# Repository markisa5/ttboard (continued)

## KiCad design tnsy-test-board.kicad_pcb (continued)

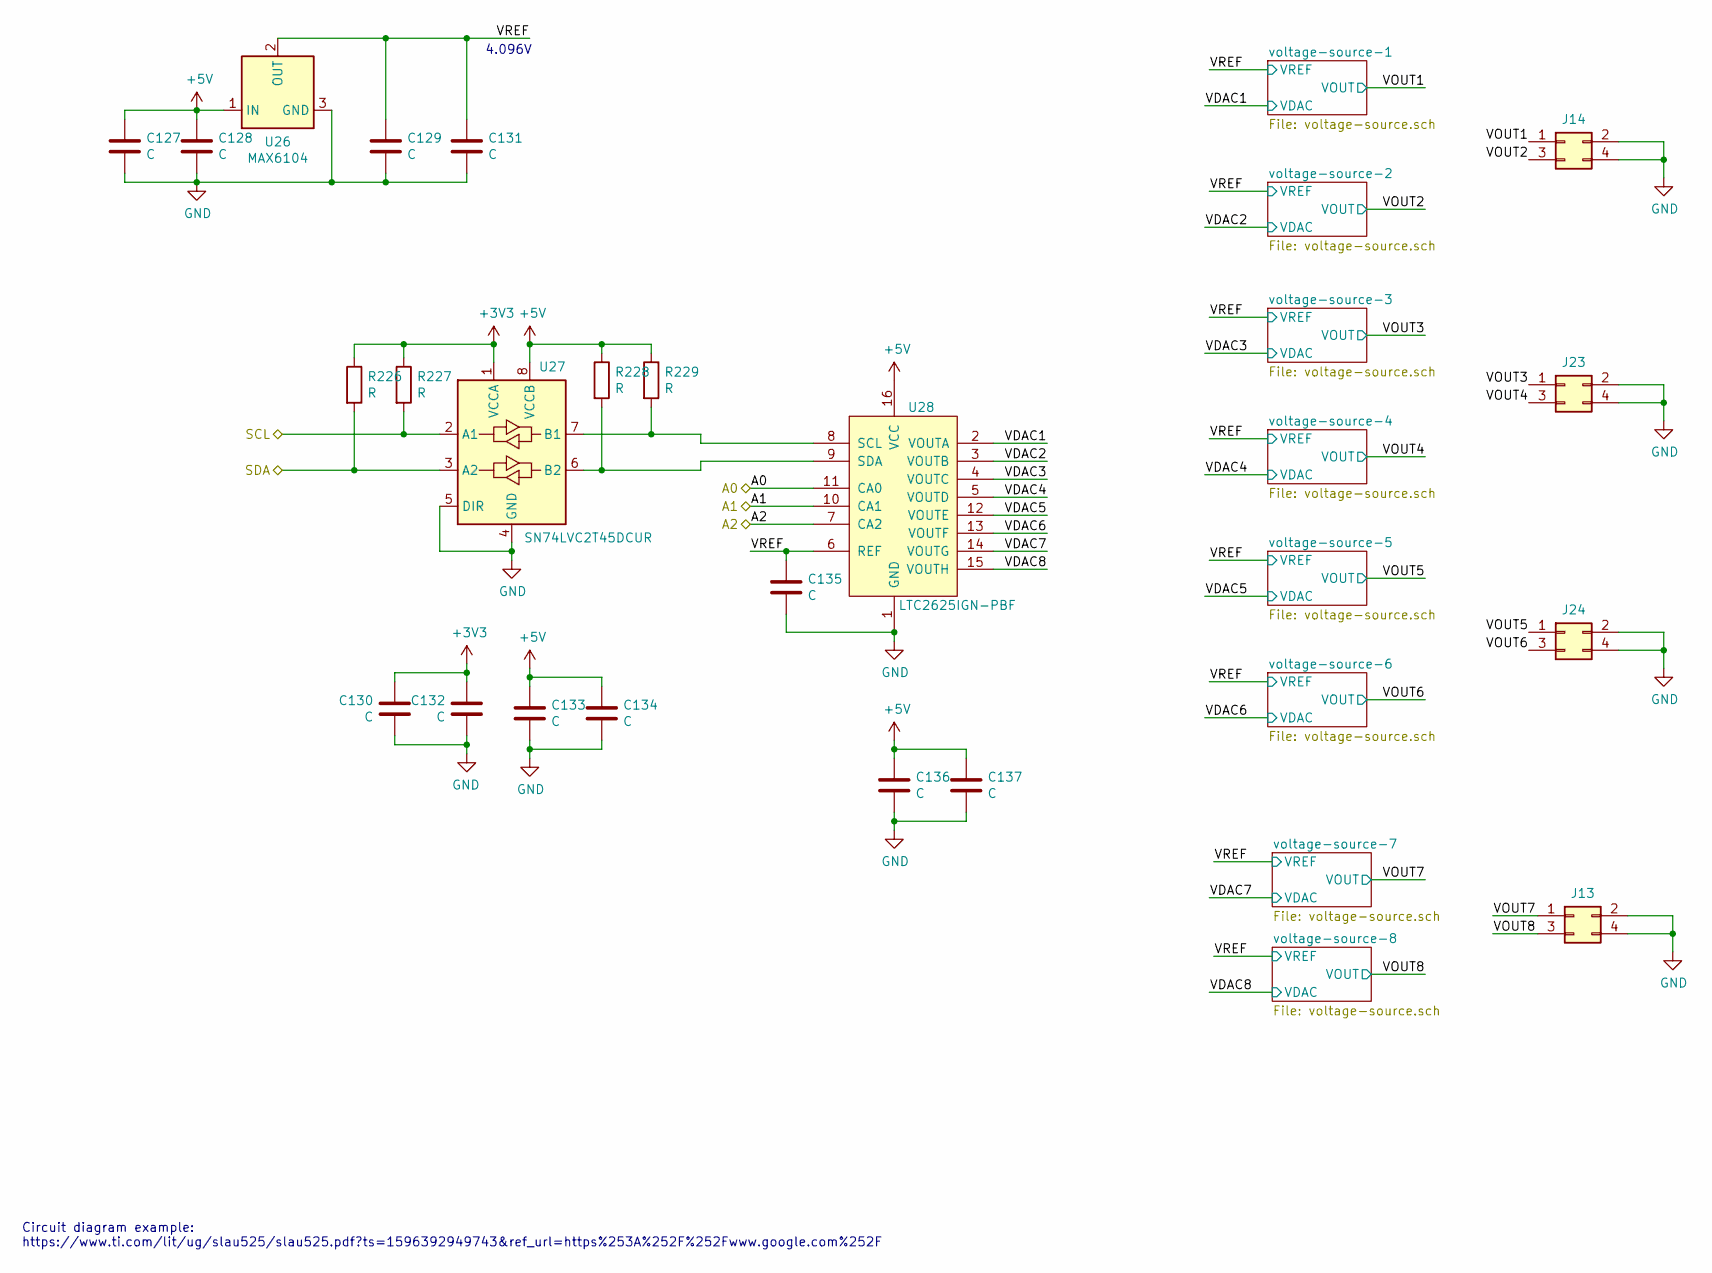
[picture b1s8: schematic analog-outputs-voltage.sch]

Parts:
C127, C128, C129, C130, C131, C132, C133, C134, C135, C136, C137: C; C_0603
J13, J14, J23, J24: Conn_02x02_Odd_Even; JST_EH_B04B-EH-A_04x2.50mm_Straight
R226, R227, R228, R229: R; R_0603
U26: MAX6104; SOT-23
U27: SN74LVC2T45DCUR; VSSOP-8_2.3x2mm_Pitch0.5mm
U28: LTC2625IGN-PBF; TSSOP-16_4.4x5mm_Pitch0.65mm

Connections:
+5V: C127.1, C128.1, C133.1, C134.1, C136.1, C137.1, R228.1, R229.1, U26.1 (IN), U27.8 (VCCB), U28.16 (VCC); also elsewhere on the board
/AO2_A0: U28.11 (CA0); also elsewhere on the board
/AO2_A1: U28.10 (CA1); also elsewhere on the board
/AO2_A2: U28.7 (CA2); also elsewhere on the board
/SCL2: R227.2, U27.2 (A1); also elsewhere on the board
/SDA2: R226.2, U27.3 (A2); also elsewhere on the board
/analog-outputs-2/VDAC1: U28.2 (VOUTA); also elsewhere on the board
/analog-outputs-2/VDAC2: U28.3 (VOUTB); also elsewhere on the board
/analog-outputs-2/VDAC3: U28.4 (VOUTC); also elsewhere on the board
/analog-outputs-2/VDAC4: U28.5 (VOUTD); also elsewhere on the board
/analog-outputs-2/VDAC5: U28.12 (VOUTE); also elsewhere on the board
/analog-outputs-2/VDAC6: U28.13 (VOUTF); also elsewhere on the board
/analog-outputs-2/VDAC7: U28.14 (VOUTG); also elsewhere on the board
/analog-outputs-2/VDAC8: U28.15 (VOUTH); also elsewhere on the board
/analog-outputs-2/VOUT1: J14.1; also elsewhere on the board
/analog-outputs-2/VOUT2: J14.3; also elsewhere on the board
/analog-outputs-2/VOUT3: J23.1; also elsewhere on the board
/analog-outputs-2/VOUT4: J23.3; also elsewhere on the board
/analog-outputs-2/VOUT5: J24.1; also elsewhere on the board
/analog-outputs-2/VOUT6: J24.3; also elsewhere on the board
/analog-outputs-2/VOUT7: J13.1; also elsewhere on the board
/analog-outputs-2/VOUT8: J13.3; also elsewhere on the board
/analog-outputs-2/VREF: C129.1, C131.1, C135.1, U26.2 (OUT), U28.6 (REF); also elsewhere on the board
GND: C127.2, C128.2, C129.2, C130.2, C131.2, C132.2, C133.2, C134.2, C135.2, C136.2, C137.2, J13.2, J13.4, J14.2, J14.4, J23.2, J23.4, J24.2, J24.4, U26.3 (GND), U27.4 (GND), U27.5 (DIR), U28.1 (GND); also elsewhere on the board
unnamed: R228.2, U27.6 (B2), U28.9 (SDA)
unnamed: R229.2, U27.7 (B1), U28.8 (SCL)

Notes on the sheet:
Circuit diagram example: https://www.ti.com/lit/ug/slau525/slau525.pdf?ts=1596392949743&ref_url=https%253A%252F%252Fwww.google.com%252F
4.096V

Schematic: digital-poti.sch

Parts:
C205: 10n; C_0603
C206, C207: 4.7u; C_0603
R287: 10k; R_0603
U39: MCP4451-103E_ST; TSSOP-20_4.4x6.5mm_Pitch0.65mm

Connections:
/DP1_A0: U39.4 (HVC/A0); also elsewhere on the board
/DP1_A1: U39.16 (A1); also elsewhere on the board
/SCL1: U39.5 (SCL); also elsewhere on the board
/SDA1: U39.6 (SDA); also elsewhere on the board
/T1A: U39.9 (P1W); also elsewhere on the board
/T1B: U39.8 (P1B); also elsewhere on the board
/T2A: U39.19 (P2W); also elsewhere on the board
/T2B: U39.18 (P2B); also elsewhere on the board
/T3A: U39.12 (P0W); also elsewhere on the board
/T3B: U39.13 (P0B); also elsewhere on the board
GND: C205.2, C206.2, C207.2, U39.7 (VSS); also elsewhere on the board
unnamed: R287.2, U39.15 (*RESET)

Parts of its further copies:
C202: 10n; C_0603
C203, C204: 4.7u; C_0603
R286: 10k; R_0603
U38: MCP4451-103E_ST; TSSOP-20_4.4x6.5mm_Pitch0.65mm

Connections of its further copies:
/DP2_A0: U38.4 (HVC/A0); also elsewhere on the board
/DP2_A1: U38.16 (A1); also elsewhere on the board
/SCL1: U38.5 (SCL); also elsewhere on the board
/SDA1: U38.6 (SDA); also elsewhere on the board
/T4A: U38.9 (P1W); also elsewhere on the board
/T4B: U38.8 (P1B); also elsewhere on the board
/T5A: U38.19 (P2W); also elsewhere on the board
/T5B: U38.18 (P2B); also elsewhere on the board
/T6A: U38.12 (P0W); also elsewhere on the board
/T6B: U38.13 (P0B); also elsewhere on the board
GND: C202.2, C203.2, C204.2, U38.7 (VSS); also elsewhere on the board
unnamed: R286.2, U38.15 (*RESET)

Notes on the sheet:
DIGITAL POTI

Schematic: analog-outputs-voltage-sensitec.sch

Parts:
C208, C209, C210, C211, C212, C213, C214, C215, C216, C217, C218: C; C_0603
J15, J16, J25, J26: Conn_02x02_Odd_Even; JST_EH_B04B-EH-A_04x2.50mm_Straight
R288, R289, R290, R291: R; R_0603
U40: MAX6104; SOT-23-3
U41: SN74LVC2T45DCUR; VSSOP-8_2.3x2mm_Pitch0.5mm
U42: LTC2625IGN-PBF; SSOP-16_3.9x4.9mm_Pitch0.635mm

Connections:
+5V: C208.1, C209.1, C214.1, C215.1, C217.1, C218.1, R290.1, R291.1, U40.1 (IN), U41.8 (VCCB), U42.16 (VCC); also elsewhere on the board
/AO3_A0: U42.11 (CA0); also elsewhere on the board
/AO3_A1: U42.10 (CA1); also elsewhere on the board
/AO3_A2: U42.7 (CA2); also elsewhere on the board
/SCL2: R289.2, U41.2 (A1); also elsewhere on the board
/SDA2: R288.2, U41.3 (A2); also elsewhere on the board
/analog-outputs-3/VDAC1: U42.2 (VOUTA); also elsewhere on the board
/analog-outputs-3/VDAC2: U42.3 (VOUTB); also elsewhere on the board
/analog-outputs-3/VDAC3: U42.4 (VOUTC); also elsewhere on the board
/analog-outputs-3/VDAC4: U42.5 (VOUTD); also elsewhere on the board
/analog-outputs-3/VDAC5: U42.12 (VOUTE); also elsewhere on the board
/analog-outputs-3/VDAC6: U42.13 (VOUTF); also elsewhere on the board
/analog-outputs-3/VDAC7: U42.14 (VOUTG); also elsewhere on the board
/analog-outputs-3/VDAC8: U42.15 (VOUTH); also elsewhere on the board
/analog-outputs-3/VOUT1: J16.1; also elsewhere on the board
/analog-outputs-3/VOUT2: J16.3; also elsewhere on the board
/analog-outputs-3/VOUT3: J25.1; also elsewhere on the board
/analog-outputs-3/VOUT4: J25.3; also elsewhere on the board
/analog-outputs-3/VOUT5: J26.1; also elsewhere on the board
/analog-outputs-3/VOUT6: J26.3; also elsewhere on the board
/analog-outputs-3/VOUT7: J15.1; also elsewhere on the board
/analog-outputs-3/VOUT8: J15.3; also elsewhere on the board
/analog-outputs-3/VREF: C210.1, C212.1, C216.1, U40.2 (OUT), U42.6 (REF); also elsewhere on the board
GND: C208.2, C209.2, C210.2, C211.2, C212.2, C213.2, C214.2, C215.2, C216.2, C217.2, C218.2, J15.2, J15.4, J16.2, J16.4, J25.2, J25.4, J26.2, J26.4, U40.3 (GND), U41.4 (GND), U41.5 (DIR), U42.1 (GND); also elsewhere on the board
unnamed: R290.2, U41.6 (B2), U42.9 (SDA)
unnamed: R291.2, U41.7 (B1), U42.8 (SCL)

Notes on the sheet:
Circuit diagram example: https://www.ti.com/lit/ug/slau525/slau525.pdf?ts=1596392949743&ref_url=https%253A%252F%252Fwww.google.com%252F
4.096V

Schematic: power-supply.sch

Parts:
C267, C268, C269, C270, C271, C272, C275, C276: C; C_0603
C273, C274: CP1; CP_Radial_D6.3mm_P2.50mm
C277, C278: 5600p; C_0603
C279, C280: 47p; C_0603
C281, C282: 100u; C_0603
C283, C285: 10u; C_0603
C284: 1u; C_0603
C286, C287: 100n; C_0603
D25: D; D_SMB
D26, D27: B560C-13-F; DO-214AB; MPN B560C-13-F; Digi-Key_PN B560C-FDICT-ND
F1: Fuse; Fuse_SMD1206_Wave
L1: L_Core_Ferrite_Coupled; CommonModeChoke_WuerthType-WE-CMB_Size-S
L2: 8.2u; Inductor_Wurth_HCI-1350
L3: 5.6u; Inductor_Wurth_HCI-1350
R324, R326: 330k; R_0603
R325, R327: 47k; R_0603
R328, R329: 162k; R_0603
R330, R331: 11.5k; R_0603
R332: 31.6k; R_0603
R333: 10.2k; R_0603
R334: 72.5k; R_0603
R335: 10k; R_0603
U51, U52: TPS54340DDA; PowerSOIC-8_W3.9mm

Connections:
+5V: C281.2, C283.2, C285.2, C287.2, L2.2, R334.1; also elsewhere on the board
+24V: F1.2; also elsewhere on the board
/power-supply/+24Vf: C267.1, C268.1, C269.1, C270.1, C271.1, C272.1, C273.1, C274.1, L1.2, R324.1, R326.1, U51.2 (VIN), U52.2 (VIN)
GND: C267.2, C268.2, C269.2, C270.2, C271.2, C272.2, C273.2, C274.2, C277.1, C278.1, C279.1, C280.1, C281.1, C282.1, C283.1, C284.1, C285.1, C286.1, C287.1, D26.A, D27.A, L1.4, R325.2, R327.2, R328.2, R329.2, R333.2, R335.2, U51.7 (GND), U51.9 (GNDPAD), U52.7 (GND), U52.9 (GNDPAD); also elsewhere on the board
GNDPWR: D25.2 (A), L1.3; also elsewhere on the board
unnamed: C275.1, U51.1 (BOOT)
unnamed: C275.2, D26.K, L2.1, U51.8 (SW)
unnamed: C276.1, U52.1 (BOOT)
unnamed: C276.2, D27.K, L3.1, U52.8 (SW)
unnamed: C277.2, R330.2
unnamed: C278.2, R331.2
unnamed: C279.2, R330.1, U51.6 (COMP)
unnamed: C280.2, R331.1, U52.6 (COMP)
unnamed: D25.1 (K), F1.1, L1.1
unnamed: R324.2, R325.1, U51.3 (EN)
unnamed: R326.2, R327.1, U52.3 (EN)
unnamed: R328.1, U51.4 (RT/CLK)
unnamed: R329.1, U52.4 (RT/CLK)
unnamed: R332.2, R333.1, U52.5 (FB)
unnamed: R334.2, R335.1, U51.5 (FB)

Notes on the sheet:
24V to 3.3V@3A
EN = pull down to disable < 1.2V
24V to 5V@3A
Add: 1. common mode filter (5Amps max design) 2. reverse polarity protection (5Amps max desing, 4Amps wcs) 3. overvoltage protection ( < 36V)

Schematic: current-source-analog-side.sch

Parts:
C18, C20, C22: 100n; C_0603
C19, C24: 4u7; C_0603
C21: 4.7u; C_0603
C23: C; C_0603
K1: EC2-3NU
Q1: SIR414DP-T1-GE3; TRANS_SQJ461EP-T1-GE3
Q2: BC817; SOT-23
Q3: Si2319BDS; SOT-23
R67, R68, R69, R70, R71: R; R_0603
R72, R73, R74: R; R_0805
U6, U7: OPA376xxD; SOIC-8_W3.9mm

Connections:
+5V: C18.1, C19.1, C20.1, C21.1, C22.1, C24.1, Q2.3 (C), U6.7 (V+), U7.7 (V+); also elsewhere on the board
/DIR1: Q2.1 (B), R69.1; also elsewhere on the board
/analog-outputs-1/A01+: K1.9; also elsewhere on the board
/analog-outputs-1/A01-: K1.4; also elsewhere on the board
/analog-outputs-1/VDAC1: U6.3 (+); also elsewhere on the board
/analog-outputs-1/current-source-1/VPOS: K1.3, K1.8, Q3.2 (S)
GND: C18.2, C19.2, C20.2, C21.2, C22.2, C24.2, K1.5, K1.10, R68.2, R69.2, R71.2, U6.4 (V-), U7.4 (V-); also elsewhere on the board
unnamed: C23.1, Q3.1 (G), R70.1, U7.6
unnamed: C23.2, R70.2, U7.2 (-)
unnamed: K1.1, Q2.2 (E)
unnamed: K1.12, R71.1
unnamed: Q1.1, Q1.2, Q1.3, R68.1, U6.2 (-)
unnamed: Q1.4, U6.6
unnamed: Q1.5, Q1.6, Q1.7, Q1.8, Q1.9, R67.2, U7.3 (+)
unnamed: Q3.3 (D), R72.2, R73.2, R74.2

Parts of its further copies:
C25, C27, C29, C32, C34, C36, C39, C41, C43, C46, C48, C50, C53, C55, C57, C60, C62, C64, C67, C69, C71: 100n; C_0603
C26, C31, C33, C38, C40, C45, C47, C52, C54, C59, C61, C66, C68, C73: 4u7; C_0603
C28, C35, C42, C49, C56, C63, C70: 4.7u; C_0603
C30, C37, C44, C51, C58, C65, C72: C; C_0603
K2, K3, K4, K5, K6, K7, K8: EC2-3NU
Q4, Q7, Q10, Q13, Q16, Q19, Q22: SIR414DP-T1-GE3; TRANS_SQJ461EP-T1-GE3
Q5, Q8, Q11, Q14, Q17, Q20, Q23: BC817; SOT-23
Q6, Q9, Q12, Q15, Q18, Q21, Q24: Si2319BDS; SOT-23
R75, R76, R77, R78, R79, R83, R84, R85, R86, R87, R91, R92, R93, R94, R95, R99, R100, R101, R102, R103, R107, R108, R109, R110, R111, R115, R116, R117, R118, R119, R123, R124, R125, R126, R127: R; R_0603
R80, R81, R82, R88, R89, R90, R96, R97, R98, R104, R105, R106, R112, R113, R114, R120, R121, R122, R128, R129, R130: R; R_0805
U8, U9, U10, U11, U12, U13, U14, U15, U16, U17, U18, U19, U20, U21: OPA376xxD; SOIC-8_W3.9mm

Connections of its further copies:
+5V: C25.1, C26.1, C27.1, C28.1, C29.1, C31.1, C32.1, C33.1, C34.1, C35.1, C36.1, C38.1, C39.1, C40.1, C41.1, C42.1, C43.1, C45.1, C46.1, C47.1, C48.1, C49.1, C50.1, C52.1, C53.1, C54.1, C55.1, C56.1, C57.1, C59.1, C60.1, C61.1, C62.1, C63.1, C64.1, C66.1, C67.1, C68.1, C69.1, C70.1, C71.1, C73.1, Q5.3 (C), Q8.3 (C), Q11.3 (C), Q14.3 (C), Q17.3 (C), Q20.3 (C), Q23.3 (C), U8.7 (V+), U9.7 (V+), U10.7 (V+), U11.7 (V+), U12.7 (V+), U13.7 (V+), U14.7 (V+), U15.7 (V+), U16.7 (V+), U17.7 (V+), U18.7 (V+), U19.7 (V+), U20.7 (V+), U21.7 (V+); also elsewhere on the board
/DIR2: Q5.1 (B), R77.1; also elsewhere on the board
/DIR3: Q8.1 (B), R85.1; also elsewhere on the board
/DIR4: Q11.1 (B), R93.1; also elsewhere on the board
/DIR5: Q14.1 (B), R101.1; also elsewhere on the board
/DIR6: Q17.1 (B), R109.1; also elsewhere on the board
/DIR7: Q20.1 (B), R117.1; also elsewhere on the board
/analog-outputs-1/A02+: K2.9; also elsewhere on the board
/analog-outputs-1/A02-: K2.4; also elsewhere on the board
/analog-outputs-1/A03+: K3.9; also elsewhere on the board
/analog-outputs-1/A03-: K3.4; also elsewhere on the board
/analog-outputs-1/A04+: K4.9; also elsewhere on the board
/analog-outputs-1/A04-: K4.4; also elsewhere on the board
/analog-outputs-1/A05+: K5.9; also elsewhere on the board
/analog-outputs-1/A05-: K5.4; also elsewhere on the board
/analog-outputs-1/A06+: K6.9; also elsewhere on the board
/analog-outputs-1/A06-: K6.4; also elsewhere on the board
/analog-outputs-1/A07+: K7.9; also elsewhere on the board
/analog-outputs-1/A07-: K7.4; also elsewhere on the board
/analog-outputs-1/A08+: K8.9; also elsewhere on the board
/analog-outputs-1/A08-: K8.4; also elsewhere on the board
/analog-outputs-1/POL8: Q23.1 (B), R125.1
/analog-outputs-1/VDAC2: U8.3 (+); also elsewhere on the board
/analog-outputs-1/VDAC3: U10.3 (+); also elsewhere on the board
/analog-outputs-1/VDAC4: U12.3 (+); also elsewhere on the board
/analog-outputs-1/VDAC5: U14.3 (+); also elsewhere on the board
/analog-outputs-1/VDAC6: U16.3 (+); also elsewhere on the board
/analog-outputs-1/VDAC7: U18.3 (+); also elsewhere on the board
/analog-outputs-1/VDAC8: U20.3 (+); also elsewhere on the board
/analog-outputs-1/current-source-2/VPOS: K2.3, K2.8, Q6.2 (S)
/analog-outputs-1/current-source-3/VPOS: K3.3, K3.8, Q9.2 (S)
/analog-outputs-1/current-source-4/VPOS: K4.3, K4.8, Q12.2 (S)
/analog-outputs-1/current-source-5/VPOS: K5.3, K5.8, Q15.2 (S)
/analog-outputs-1/current-source-6/VPOS: K6.3, K6.8, Q18.2 (S)
/analog-outputs-1/current-source-spare-1/VPOS: K7.3, K7.8, Q21.2 (S)
/analog-outputs-1/current-source-spare-2/VPOS: K8.3, K8.8, Q24.2 (S)
GND: C25.2, C26.2, C27.2, C28.2, C29.2, C31.2, C32.2, C33.2, C34.2, C35.2, C36.2, C38.2, C39.2, C40.2, C41.2, C42.2, C43.2, C45.2, C46.2, C47.2, C48.2, C49.2, C50.2, C52.2, C53.2, C54.2, C55.2, C56.2, C57.2, C59.2, C60.2, C61.2, C62.2, C63.2, C64.2, C66.2, C67.2, C68.2, C69.2, C70.2, C71.2, C73.2, K2.5, K2.10, K3.5, K3.10, K4.5, K4.10, K5.5, K5.10, K6.5, K6.10, K7.5, K7.10, K8.5, K8.10, R76.2, R77.2, R79.2, R84.2, R85.2, R87.2, R92.2, R93.2, R95.2, R100.2, R101.2, R103.2, R108.2, R109.2, R111.2, R116.2, R117.2, R119.2, R124.2, R125.2, R127.2, U8.4 (V-), U9.4 (V-), U10.4 (V-), U11.4 (V-), U12.4 (V-), U13.4 (V-), U14.4 (V-), U15.4 (V-), U16.4 (V-), U17.4 (V-), U18.4 (V-), U19.4 (V-), U20.4 (V-), U21.4 (V-); also elsewhere on the board
unnamed: C30.1, Q6.1 (G), R78.1, U9.6
unnamed: C30.2, R78.2, U9.2 (-)
unnamed: C37.1, Q9.1 (G), R86.1, U11.6
unnamed: C37.2, R86.2, U11.2 (-)
unnamed: C44.1, Q12.1 (G), R94.1, U13.6
unnamed: C44.2, R94.2, U13.2 (-)
unnamed: C51.1, Q15.1 (G), R102.1, U15.6
unnamed: C51.2, R102.2, U15.2 (-)
unnamed: C58.1, Q18.1 (G), R110.1, U17.6
unnamed: C58.2, R110.2, U17.2 (-)
unnamed: C65.1, Q21.1 (G), R118.1, U19.6
unnamed: C65.2, R118.2, U19.2 (-)
unnamed: C72.1, Q24.1 (G), R126.1, U21.6
unnamed: C72.2, R126.2, U21.2 (-)
unnamed: K2.1, Q5.2 (E)
unnamed: K2.12, R79.1
unnamed: K3.1, Q8.2 (E)
unnamed: K3.12, R87.1
unnamed: K4.1, Q11.2 (E)
unnamed: K4.12, R95.1
unnamed: K5.1, Q14.2 (E)
unnamed: K5.12, R103.1
unnamed: K6.1, Q17.2 (E)
unnamed: K6.12, R111.1
unnamed: K7.1, Q20.2 (E)
unnamed: K7.12, R119.1
unnamed: K8.1, Q23.2 (E)
unnamed: K8.12, R127.1
unnamed: Q4.1, Q4.2, Q4.3, R76.1, U8.2 (-)
unnamed: Q4.4, U8.6
unnamed: Q4.5, Q4.6, Q4.7, Q4.8, Q4.9, R75.2, U9.3 (+)
unnamed: Q6.3 (D), R80.2, R81.2, R82.2
unnamed: Q7.1, Q7.2, Q7.3, R84.1, U10.2 (-)
unnamed: Q7.4, U10.6
unnamed: Q7.5, Q7.6, Q7.7, Q7.8, Q7.9, R83.2, U11.3 (+)
unnamed: Q9.3 (D), R88.2, R89.2, R90.2
unnamed: Q10.1, Q10.2, Q10.3, R92.1, U12.2 (-)
unnamed: Q10.4, U12.6
unnamed: Q10.5, Q10.6, Q10.7, Q10.8, Q10.9, R91.2, U13.3 (+)
unnamed: Q12.3 (D), R96.2, R97.2, R98.2
unnamed: Q13.1, Q13.2, Q13.3, R100.1, U14.2 (-)
unnamed: Q13.4, U14.6
unnamed: Q13.5, Q13.6, Q13.7, Q13.8, Q13.9, R99.2, U15.3 (+)
unnamed: Q15.3 (D), R104.2, R105.2, R106.2
unnamed: Q16.1, Q16.2, Q16.3, R108.1, U16.2 (-)
unnamed: Q16.4, U16.6
unnamed: Q16.5, Q16.6, Q16.7, Q16.8, Q16.9, R107.2, U17.3 (+)
unnamed: Q18.3 (D), R112.2, R113.2, R114.2
unnamed: Q19.1, Q19.2, Q19.3, R116.1, U18.2 (-)
unnamed: Q19.4, U18.6
unnamed: Q19.5, Q19.6, Q19.7, Q19.8, Q19.9, R115.2, U19.3 (+)
unnamed: Q21.3 (D), R120.2, R121.2, R122.2
unnamed: Q22.1, Q22.2, Q22.3, R124.1, U20.2 (-)
unnamed: Q22.4, U20.6
unnamed: Q22.5, Q22.6, Q22.7, Q22.8, Q22.9, R123.2, U21.3 (+)
unnamed: Q24.3 (D), R128.2, R129.2, R130.2

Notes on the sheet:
RLOAD
3.3V

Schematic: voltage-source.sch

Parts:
C138, C139, C140, C141, C142, C143: C; C_0603
R230, R231, R232, R233: R; R_0603
U29: OPA188xxD; SOIC-8_W3.9mm

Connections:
+5V: C140.2, C142.2, U29.7 (V+); also elsewhere on the board
/analog-outputs-2/VDAC1: U29.3 (+); also elsewhere on the board
/analog-outputs-2/VOUT1: C143.2, R232.1, R233.1; also elsewhere on the board
/analog-outputs-2/VREF: R230.2; also elsewhere on the board
GND: C138.1, C140.1, C141.1, C142.1, C143.1, R231.1; also elsewhere on the board
unnamed: C138.2, C141.2, U29.4 (V-)
unnamed: C139.1, R233.2, U29.6
unnamed: C139.2, R230.1, R231.2, R232.2, U29.2 (-)

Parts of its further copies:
C144, C145, C146, C147, C148, C149, C150, C151, C152, C153, C154, C155, C156, C157, C158, C159, C160, C161, C162, C163, C164, C165, C166, C167, C168, C169, C170, C171, C172, C173, C174, C175, C176, C177, C178, C179, C180, C181, C182, C183, C184, C185, C219, C220, C221, C222, C223, C224, C225, C226, C227, C228, C229, C230, C231, C232, C233, C234, C235, C236, C237, C238, C239, C240, C241, C242, C243, C244, C245, C246, C247, C248, C249, C250, C251, C252, C253, C254, C255, C256, C257, C258, C259, C260, C261, C262, C263, C264, C265, C266: C; C_0603
R234, R235, R236, R237, R238, R239, R240, R241, R242, R243, R244, R245, R246, R247, R248, R249, R250, R251, R252, R253, R254, R255, R256, R257, R258, R259, R260, R261, R292, R293, R294, R295, R296, R297, R298, R299, R300, R301, R302, R303, R304, R305, R306, R307, R308, R309, R310, R311, R312, R313, R314, R315, R316, R317, R318, R319, R320, R321, R322, R323: R; R_0603
U30, U31, U32, U33, U34, U35, U36, U43, U44, U45, U46, U47, U48, U49, U50: OPA188xxD; SOIC-8_W3.9mm

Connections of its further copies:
+5V: C146.2, C148.2, C152.2, C154.2, C158.2, C160.2, C164.2, C166.2, C170.2, C172.2, C176.2, C178.2, C182.2, C184.2, C221.2, C223.2, C227.2, C229.2, C233.2, C235.2, C239.2, C241.2, C245.2, C247.2, C251.2, C253.2, C257.2, C259.2, C263.2, C265.2, U30.7 (V+), U31.7 (V+), U32.7 (V+), U33.7 (V+), U34.7 (V+), U35.7 (V+), U36.7 (V+), U43.7 (V+), U44.7 (V+), U45.7 (V+), U46.7 (V+), U47.7 (V+), U48.7 (V+), U49.7 (V+), U50.7 (V+); also elsewhere on the board
/analog-outputs-2/VDAC2: U30.3 (+); also elsewhere on the board
/analog-outputs-2/VDAC3: U31.3 (+); also elsewhere on the board
/analog-outputs-2/VDAC4: U32.3 (+); also elsewhere on the board
/analog-outputs-2/VDAC5: U33.3 (+); also elsewhere on the board
/analog-outputs-2/VDAC6: U34.3 (+); also elsewhere on the board
/analog-outputs-2/VDAC7: U35.3 (+); also elsewhere on the board
/analog-outputs-2/VDAC8: U36.3 (+); also elsewhere on the board
/analog-outputs-2/VOUT2: C149.2, R236.1, R237.1; also elsewhere on the board
/analog-outputs-2/VOUT3: C155.2, R240.1, R241.1; also elsewhere on the board
/analog-outputs-2/VOUT4: C161.2, R244.1, R245.1; also elsewhere on the board
/analog-outputs-2/VOUT5: C167.2, R248.1, R249.1; also elsewhere on the board
/analog-outputs-2/VOUT6: C173.2, R252.1, R253.1; also elsewhere on the board
/analog-outputs-2/VOUT7: C179.2, R256.1, R257.1; also elsewhere on the board
/analog-outputs-2/VOUT8: C185.2, R260.1, R261.1; also elsewhere on the board
/analog-outputs-2/VREF: R234.2, R238.2, R242.2, R246.2, R250.2, R254.2, R258.2; also elsewhere on the board
/analog-outputs-3/VDAC1: U43.3 (+); also elsewhere on the board
/analog-outputs-3/VDAC2: U44.3 (+); also elsewhere on the board
/analog-outputs-3/VDAC3: U45.3 (+); also elsewhere on the board
/analog-outputs-3/VDAC4: U46.3 (+); also elsewhere on the board
/analog-outputs-3/VDAC5: U47.3 (+); also elsewhere on the board
/analog-outputs-3/VDAC6: U48.3 (+); also elsewhere on the board
/analog-outputs-3/VDAC7: U49.3 (+); also elsewhere on the board
/analog-outputs-3/VDAC8: U50.3 (+); also elsewhere on the board
/analog-outputs-3/VOUT1: C224.2, R294.1, R295.1; also elsewhere on the board
/analog-outputs-3/VOUT2: C230.2, R298.1, R299.1; also elsewhere on the board
/analog-outputs-3/VOUT3: C236.2, R302.1, R303.1; also elsewhere on the board
/analog-outputs-3/VOUT4: C242.2, R306.1, R307.1; also elsewhere on the board
/analog-outputs-3/VOUT5: C248.2, R310.1, R311.1; also elsewhere on the board
/analog-outputs-3/VOUT6: C254.2, R314.1, R315.1; also elsewhere on the board
/analog-outputs-3/VOUT7: C260.2, R318.1, R319.1; also elsewhere on the board
/analog-outputs-3/VOUT8: C266.2, R322.1, R323.1; also elsewhere on the board
/analog-outputs-3/VREF: R292.2, R296.2, R300.2, R304.2, R308.2, R312.2, R316.2, R320.2; also elsewhere on the board
GND: C144.1, C146.1, C147.1, C148.1, C149.1, C150.1, C152.1, C153.1, C154.1, C155.1, C156.1, C158.1, C159.1, C160.1, C161.1, C162.1, C164.1, C165.1, C166.1, C167.1, C168.1, C170.1, C171.1, C172.1, C173.1, C174.1, C176.1, C177.1, C178.1, C179.1, C180.1, C182.1, C183.1, C184.1, C185.1, C219.1, C221.1, C222.1, C223.1, C224.1, C225.1, C227.1, C228.1, C229.1, C230.1, C231.1, C233.1, C234.1, C235.1, C236.1, C237.1, C239.1, C240.1, C241.1, C242.1, C243.1, C245.1, C246.1, C247.1, C248.1, C249.1, C251.1, C252.1, C253.1, C254.1, C255.1, C257.1, C258.1, C259.1, C260.1, C261.1, C263.1, C264.1, C265.1, C266.1, R235.1, R239.1, R243.1, R247.1, R251.1, R255.1, R259.1, R293.1, R297.1, R301.1, R305.1, R309.1, R313.1, R317.1, R321.1; also elsewhere on the board
unnamed: C144.2, C147.2, U30.4 (V-)
unnamed: C145.1, R237.2, U30.6
unnamed: C145.2, R234.1, R235.2, R236.2, U30.2 (-)
unnamed: C150.2, C153.2, U31.4 (V-)
unnamed: C151.1, R241.2, U31.6
unnamed: C151.2, R238.1, R239.2, R240.2, U31.2 (-)
unnamed: C156.2, C159.2, U32.4 (V-)
unnamed: C157.1, R245.2, U32.6
unnamed: C157.2, R242.1, R243.2, R244.2, U32.2 (-)
unnamed: C162.2, C165.2, U33.4 (V-)
unnamed: C163.1, R249.2, U33.6
unnamed: C163.2, R246.1, R247.2, R248.2, U33.2 (-)
unnamed: C168.2, C171.2, U34.4 (V-)
unnamed: C169.1, R253.2, U34.6
unnamed: C169.2, R250.1, R251.2, R252.2, U34.2 (-)
unnamed: C174.2, C177.2, U35.4 (V-)
unnamed: C175.1, R257.2, U35.6
unnamed: C175.2, R254.1, R255.2, R256.2, U35.2 (-)
unnamed: C180.2, C183.2, U36.4 (V-)
unnamed: C181.1, R261.2, U36.6
unnamed: C181.2, R258.1, R259.2, R260.2, U36.2 (-)
unnamed: C219.2, C222.2, U43.4 (V-)
unnamed: C220.1, R295.2, U43.6
unnamed: C220.2, R292.1, R293.2, R294.2, U43.2 (-)
unnamed: C225.2, C228.2, U44.4 (V-)
unnamed: C226.1, R299.2, U44.6
unnamed: C226.2, R296.1, R297.2, R298.2, U44.2 (-)
unnamed: C231.2, C234.2, U45.4 (V-)
unnamed: C232.1, R303.2, U45.6
unnamed: C232.2, R300.1, R301.2, R302.2, U45.2 (-)
unnamed: C237.2, C240.2, U46.4 (V-)
unnamed: C238.1, R307.2, U46.6
unnamed: C238.2, R304.1, R305.2, R306.2, U46.2 (-)
unnamed: C243.2, C246.2, U47.4 (V-)
unnamed: C244.1, R311.2, U47.6
unnamed: C244.2, R308.1, R309.2, R310.2, U47.2 (-)
unnamed: C249.2, C252.2, U48.4 (V-)
unnamed: C250.1, R315.2, U48.6
unnamed: C250.2, R312.1, R313.2, R314.2, U48.2 (-)
unnamed: C255.2, C258.2, U49.4 (V-)
unnamed: C256.1, R319.2, U49.6
unnamed: C256.2, R316.1, R317.2, R318.2, U49.2 (-)
unnamed: C261.2, C264.2, U50.4 (V-)
unnamed: C262.1, R323.2, U50.6
unnamed: C262.2, R320.1, R321.2, R322.2, U50.2 (-)

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
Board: 2 copper layers, 795 parts (0 on the bottom side), 393 nets, no tracks yet.
